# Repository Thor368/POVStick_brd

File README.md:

POVStick

This is a Persistance Of Vision display in form of a NeoPixel stick. In the future this will be a much shorter and denser handheld LED strip. A SLR will be used in long time exposure mode to "stitch" the image back together as the stick is moved across its field of vision.

The image is stored on a SD card and read by an AVR. The display itself is a string of WS2812 Pixel LEDs. At this (unoptimized) state the AVR is capable of displaying around 75 lines per second at 288 LEDs per line.

Current state: https://youtu.be/oT6iY_f27Is

# Board
The current relase V1.0 is currently in production. The board dimensions are 73x19mm² and feautre:
- ATmega1284 (8kB RAM) @12MHz
- microSD slot
- sleep mode (LED throw-off)
- 4 button inputs
- I²C for small OLED displays
- max. 18V input voltage

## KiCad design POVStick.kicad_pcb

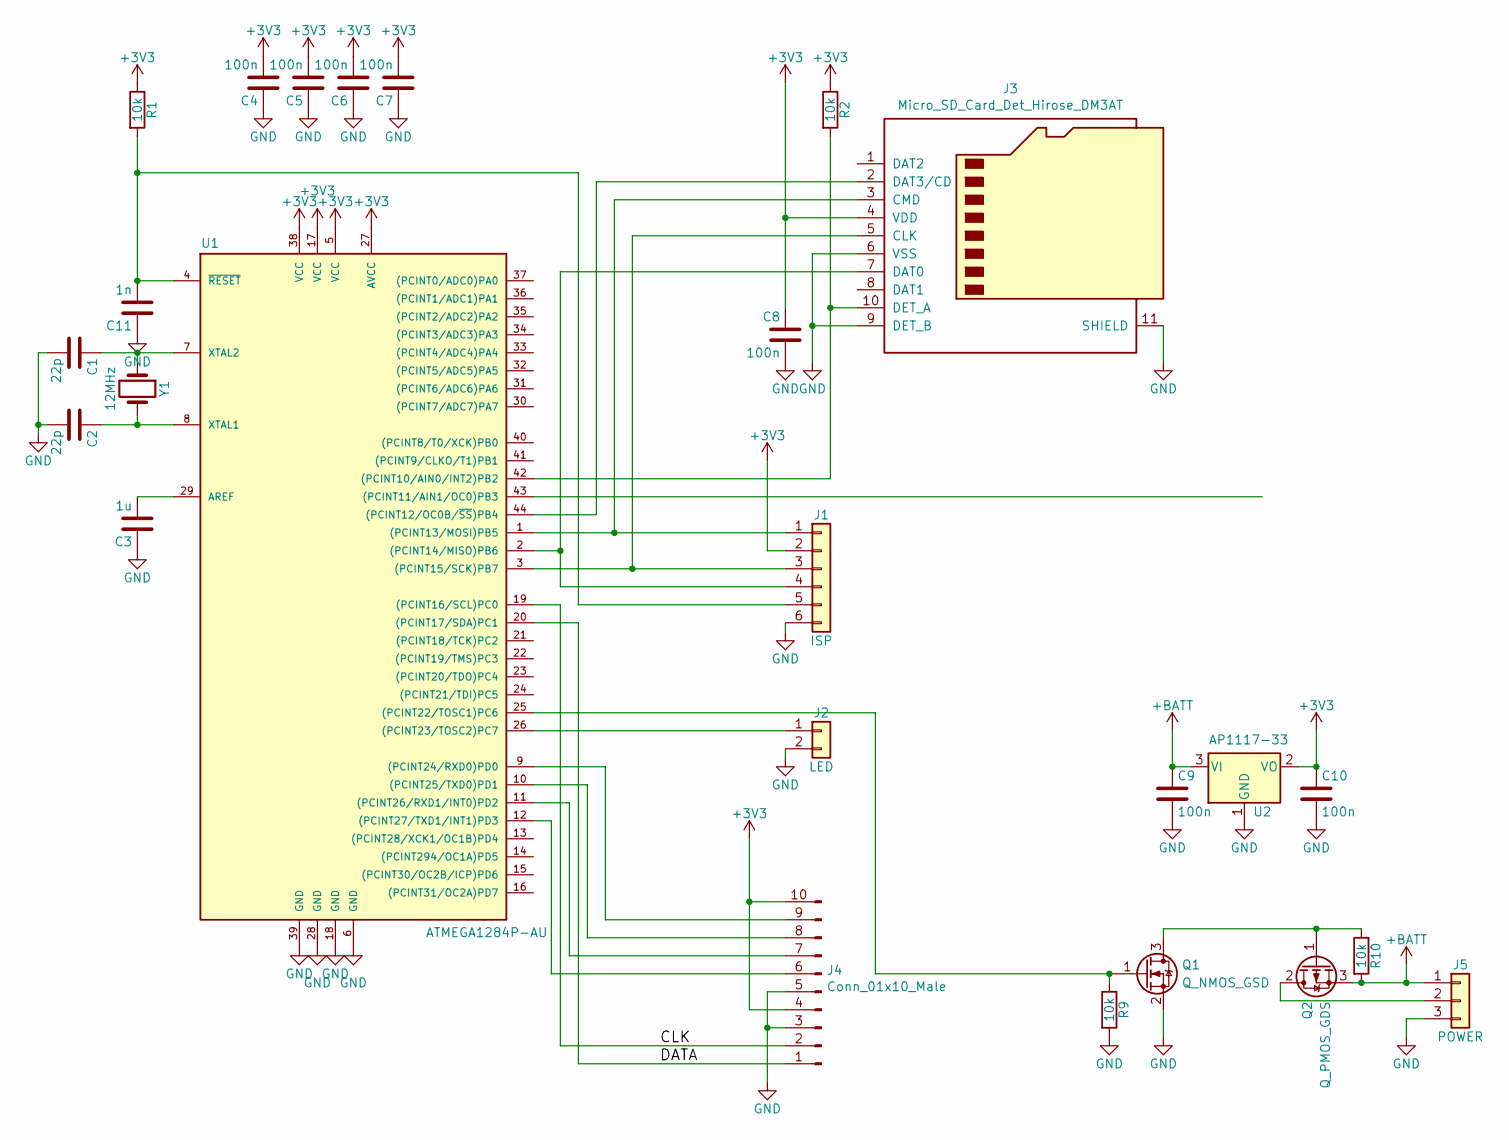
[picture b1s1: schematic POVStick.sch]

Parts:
C1, C2: 22p; C_0805_2012Metric
C3: 1u; C_0805_2012Metric
C4, C5, C6, C7, C8, C9, C10: 100n; C_0805_2012Metric
C11: 1n; C_0805_2012Metric
J1: ISP; PinHeader_2x03_P2.54mm_Vertical
J2: LED; PinHeader_1x02_P2.54mm_Vertical
J3: Micro_SD_Card_Det_Hirose_DM3AT; microSD_HC_Hirose_DM3D-SF
J4: Conn_01x10_Male; PinSocket_1x10_P2.54mm_Vertical
J5: POWER; TerminalBlock_bornier-3_P5.08mm
Q1: Q_NMOS_GSD; SOT-23
Q2: Q_PMOS_GDS; TO-252-2
R1, R2, R9, R10: 10k; R_0805_2012Metric
U1: ATMEGA1284P-AU; LQFP-44_10x10mm_P0.8mm
U2: AP1117-33; SOT-223-3_TabPin2
Y1: 12MHz; Crystal_HC49-U_Vertical

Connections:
+3V3: C4.2, C5.2, C6.2, C7.2, C8.1, C10.1, J1.2, J3.4 (VDD), J4.4, J4.10, R1.1, R2.1, U1.5 (VCC), U1.17 (VCC), U1.27 (AVCC), U1.38 (VCC), U2.2 (VO)
+BATT: C9.1, J5.1, Q2.3 (S), R10.2, U2.3 (VI)
/CLK: J4.2, U1.19 ((PCINT16/SCL)PC0)
/DATA: J4.1, U1.20 ((PCINT17/SDA)PC1)
GND: C1.2, C2.2, C3.1, C4.1, C5.1, C6.1, C7.1, C8.2, C9.2, C10.2, C11.1, J1.6, J2.2, J3.6 (VSS), J3.9 (DET_B), J3.11 (SHIELD), J4.3, J4.5, J5.3, Q1.2 (S), R9.2, U1.6 (GND), U1.18 (GND), U1.28 (GND), U1.39 (GND), U2.1 (GND)
unnamed: C1.1, U1.7 (XTAL2), Y1.1
unnamed: C2.1, U1.8 (XTAL1), Y1.2
unnamed: C3.2, U1.29 (AREF)
unnamed: C11.2, J1.5, R1.2, U1.4 (~RESET)
unnamed: J1.1, J3.3 (CMD), U1.1 ((PCINT13/MOSI)PB5)
unnamed: J1.3, J3.5 (CLK), U1.3 ((PCINT15/SCK)PB7)
unnamed: J1.4, J3.7 (DAT0), U1.2 ((PCINT14/MISO)PB6)
unnamed: J2.1, U1.26 ((PCINT23/TOSC2)PC7)
unnamed: J3.2 (DAT3/CD), U1.44 ((PCINT12/OC0B/~SS~)PB4)
unnamed: J3.10 (DET_A), R2.2, U1.42 ((PCINT10/AIN0/INT2)PB2)
unnamed: J4.6, U1.12 ((PCINT27/TXD1/INT1)PD3)
unnamed: J4.7, U1.11 ((PCINT26/RXD1/INT0)PD2)
unnamed: J4.8, U1.10 ((PCINT25/TXD0)PD1)
unnamed: J4.9, U1.9 ((PCINT24/RXD0)PD0)
unnamed: J5.2, Q2.2 (D)
unnamed: Q1.1 (G), R9.1, U1.25 ((PCINT22/TOSC1)PC6)
unnamed: Q1.3 (D), Q2.1 (G), R10.1

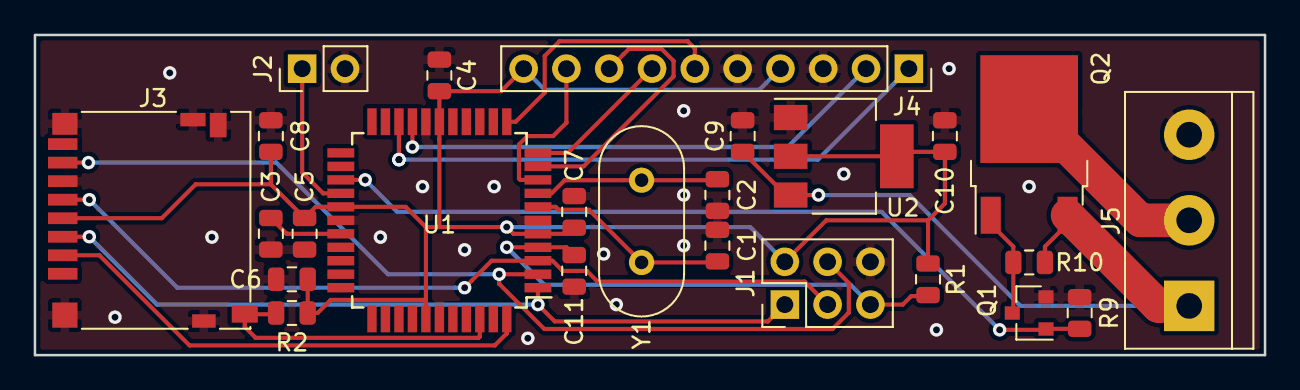
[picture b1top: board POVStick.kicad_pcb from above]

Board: 2 copper layers, 73.0 x 19.0 mm, 25 parts (0 on the bottom side), 22 nets.

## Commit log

2018-01-03 - added a description in README.md - schematic is pretty much complete - footprints are mostly selected - missing a footprint for a micro sd card slot, tho -> problem for future thor
2018-06-28 - changed design over to UI connector instead of dedicated keys and OLED - added power fet to switch Vbat for LEDs - added 3V3 reg
2019-03-21 - changed SD socket - removed pull-ups - changed pinout of IO jack - routed the layout
2019-03-22 - added home point - added GEBERBER to .gitignore - moved a REF - base for V1.0
2019-04-10 - updated readme with info about V1.0
2019-04-10 - added max input voltage to readme
